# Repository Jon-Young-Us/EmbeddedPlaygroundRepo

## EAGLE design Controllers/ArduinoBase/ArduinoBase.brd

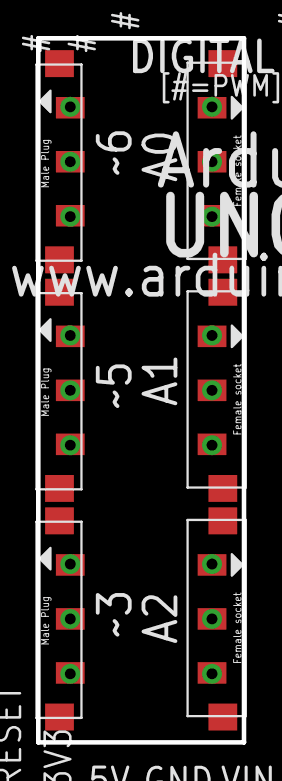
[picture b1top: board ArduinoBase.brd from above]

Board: 2 copper layers, 11.4 x 39.1 mm, 6 parts (0 on the bottom side), 2 nets, no tracks yet.

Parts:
U$1, U$5, U$6: CONN-SOCKET-3POS-3MM; SOCKET-3POS-3MM-SMD
U$2, U$3, U$4: CONN-PLUG-3POS-3MM; PLUG-3POS-3MM-SMD

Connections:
GND: U$1.GND, U$2.GND, U$3.GND, U$4.GND, U$5.GND, U$6.GND
VCC: U$1.VCC, U$2.VCC, U$3.VCC, U$4.VCC, U$5.VCC, U$6.VCC

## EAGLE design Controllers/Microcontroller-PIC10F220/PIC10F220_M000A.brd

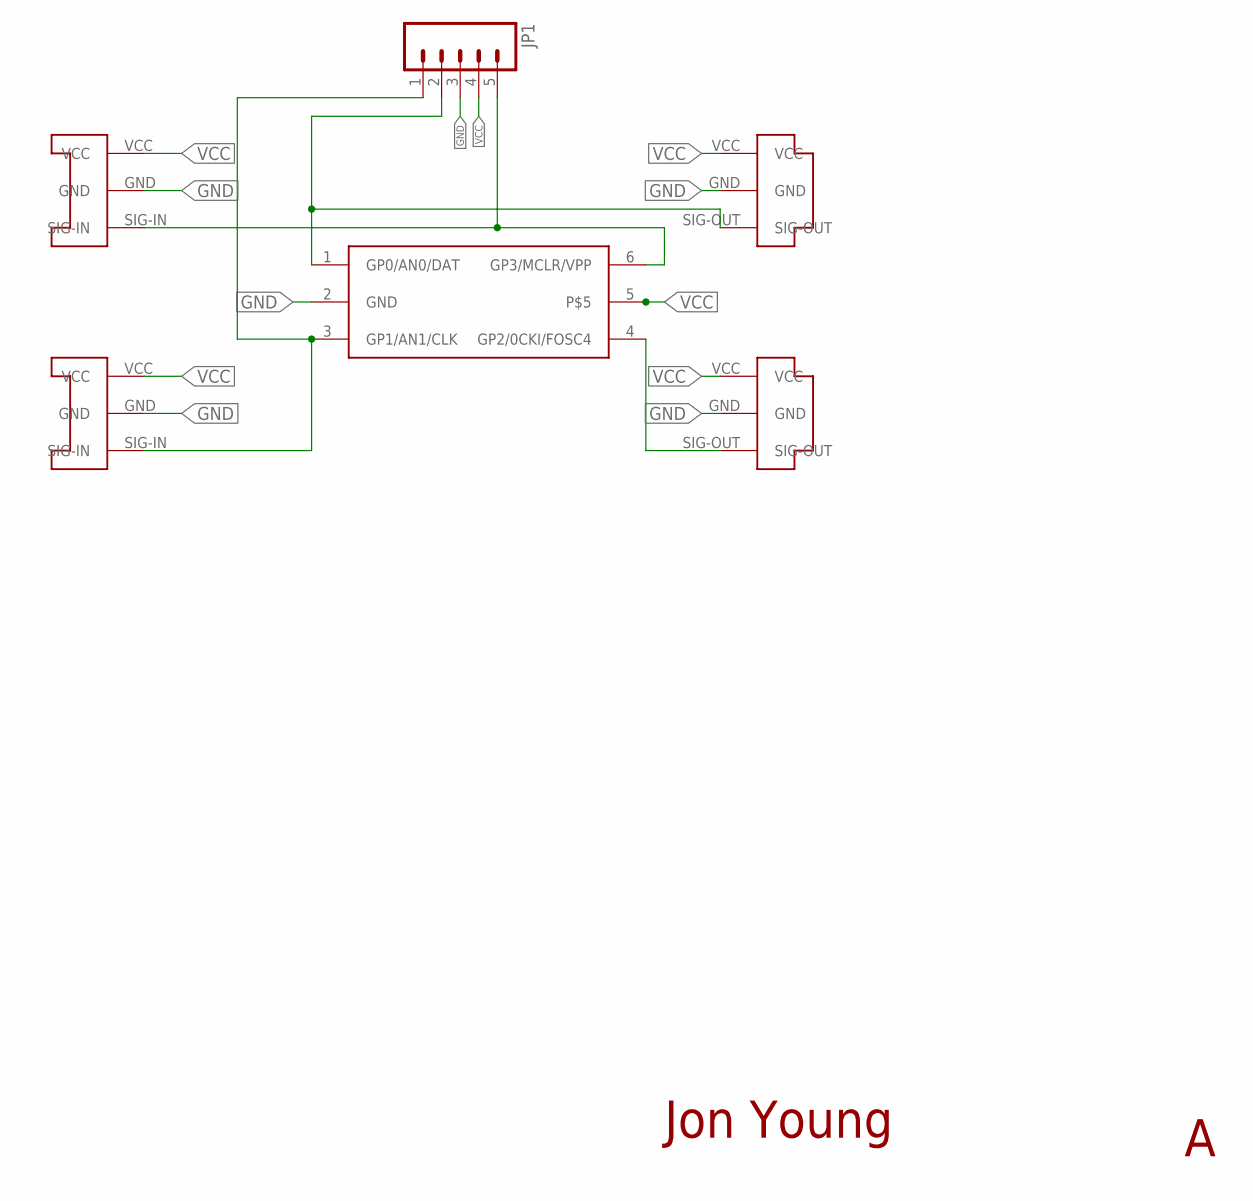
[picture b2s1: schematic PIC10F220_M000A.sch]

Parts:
JP1: M051.27MM; 1X05-1.27MM
U$1, U$4: CONN-PLUG-3POS-3MM; PLUG-3POS-3MM-SMD
U$2, U$3: CONN-SOCKET-3POS-3MM; SOCKET-3POS-3MM-SMD
U$5: PIC10F2XXT-I/OT; SOT23-6

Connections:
GND: JP1.3, U$1.GND, U$2.GND, U$3.GND, U$4.GND, U$5.2 (GND)
unnamed: U$1.SIG-OUT, U$5.4 (GP2/0CKI/FOSC4)
unnamed: JP1.1, U$2.SIG-IN, U$5.3 (GP1/AN1/CLK)
unnamed: JP1.2, U$4.SIG-OUT, U$5.1 (GP0/AN0/DAT)
unnamed: JP1.5, U$3.SIG-IN, U$5.6 (GP3/MCLR/VPP)
VCC: JP1.4, U$1.VCC, U$2.VCC, U$3.VCC, U$4.VCC, U$5.5

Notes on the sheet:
Jon Young

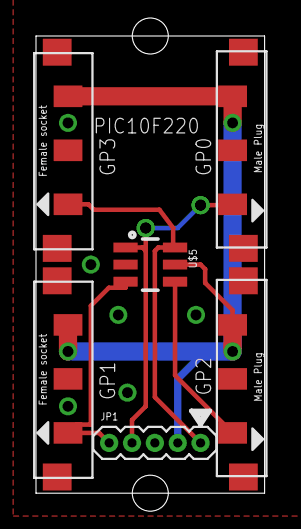
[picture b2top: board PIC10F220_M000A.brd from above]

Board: 2 copper layers, 12.7 x 25.4 mm, 6 parts (0 on the bottom side), 6 nets.

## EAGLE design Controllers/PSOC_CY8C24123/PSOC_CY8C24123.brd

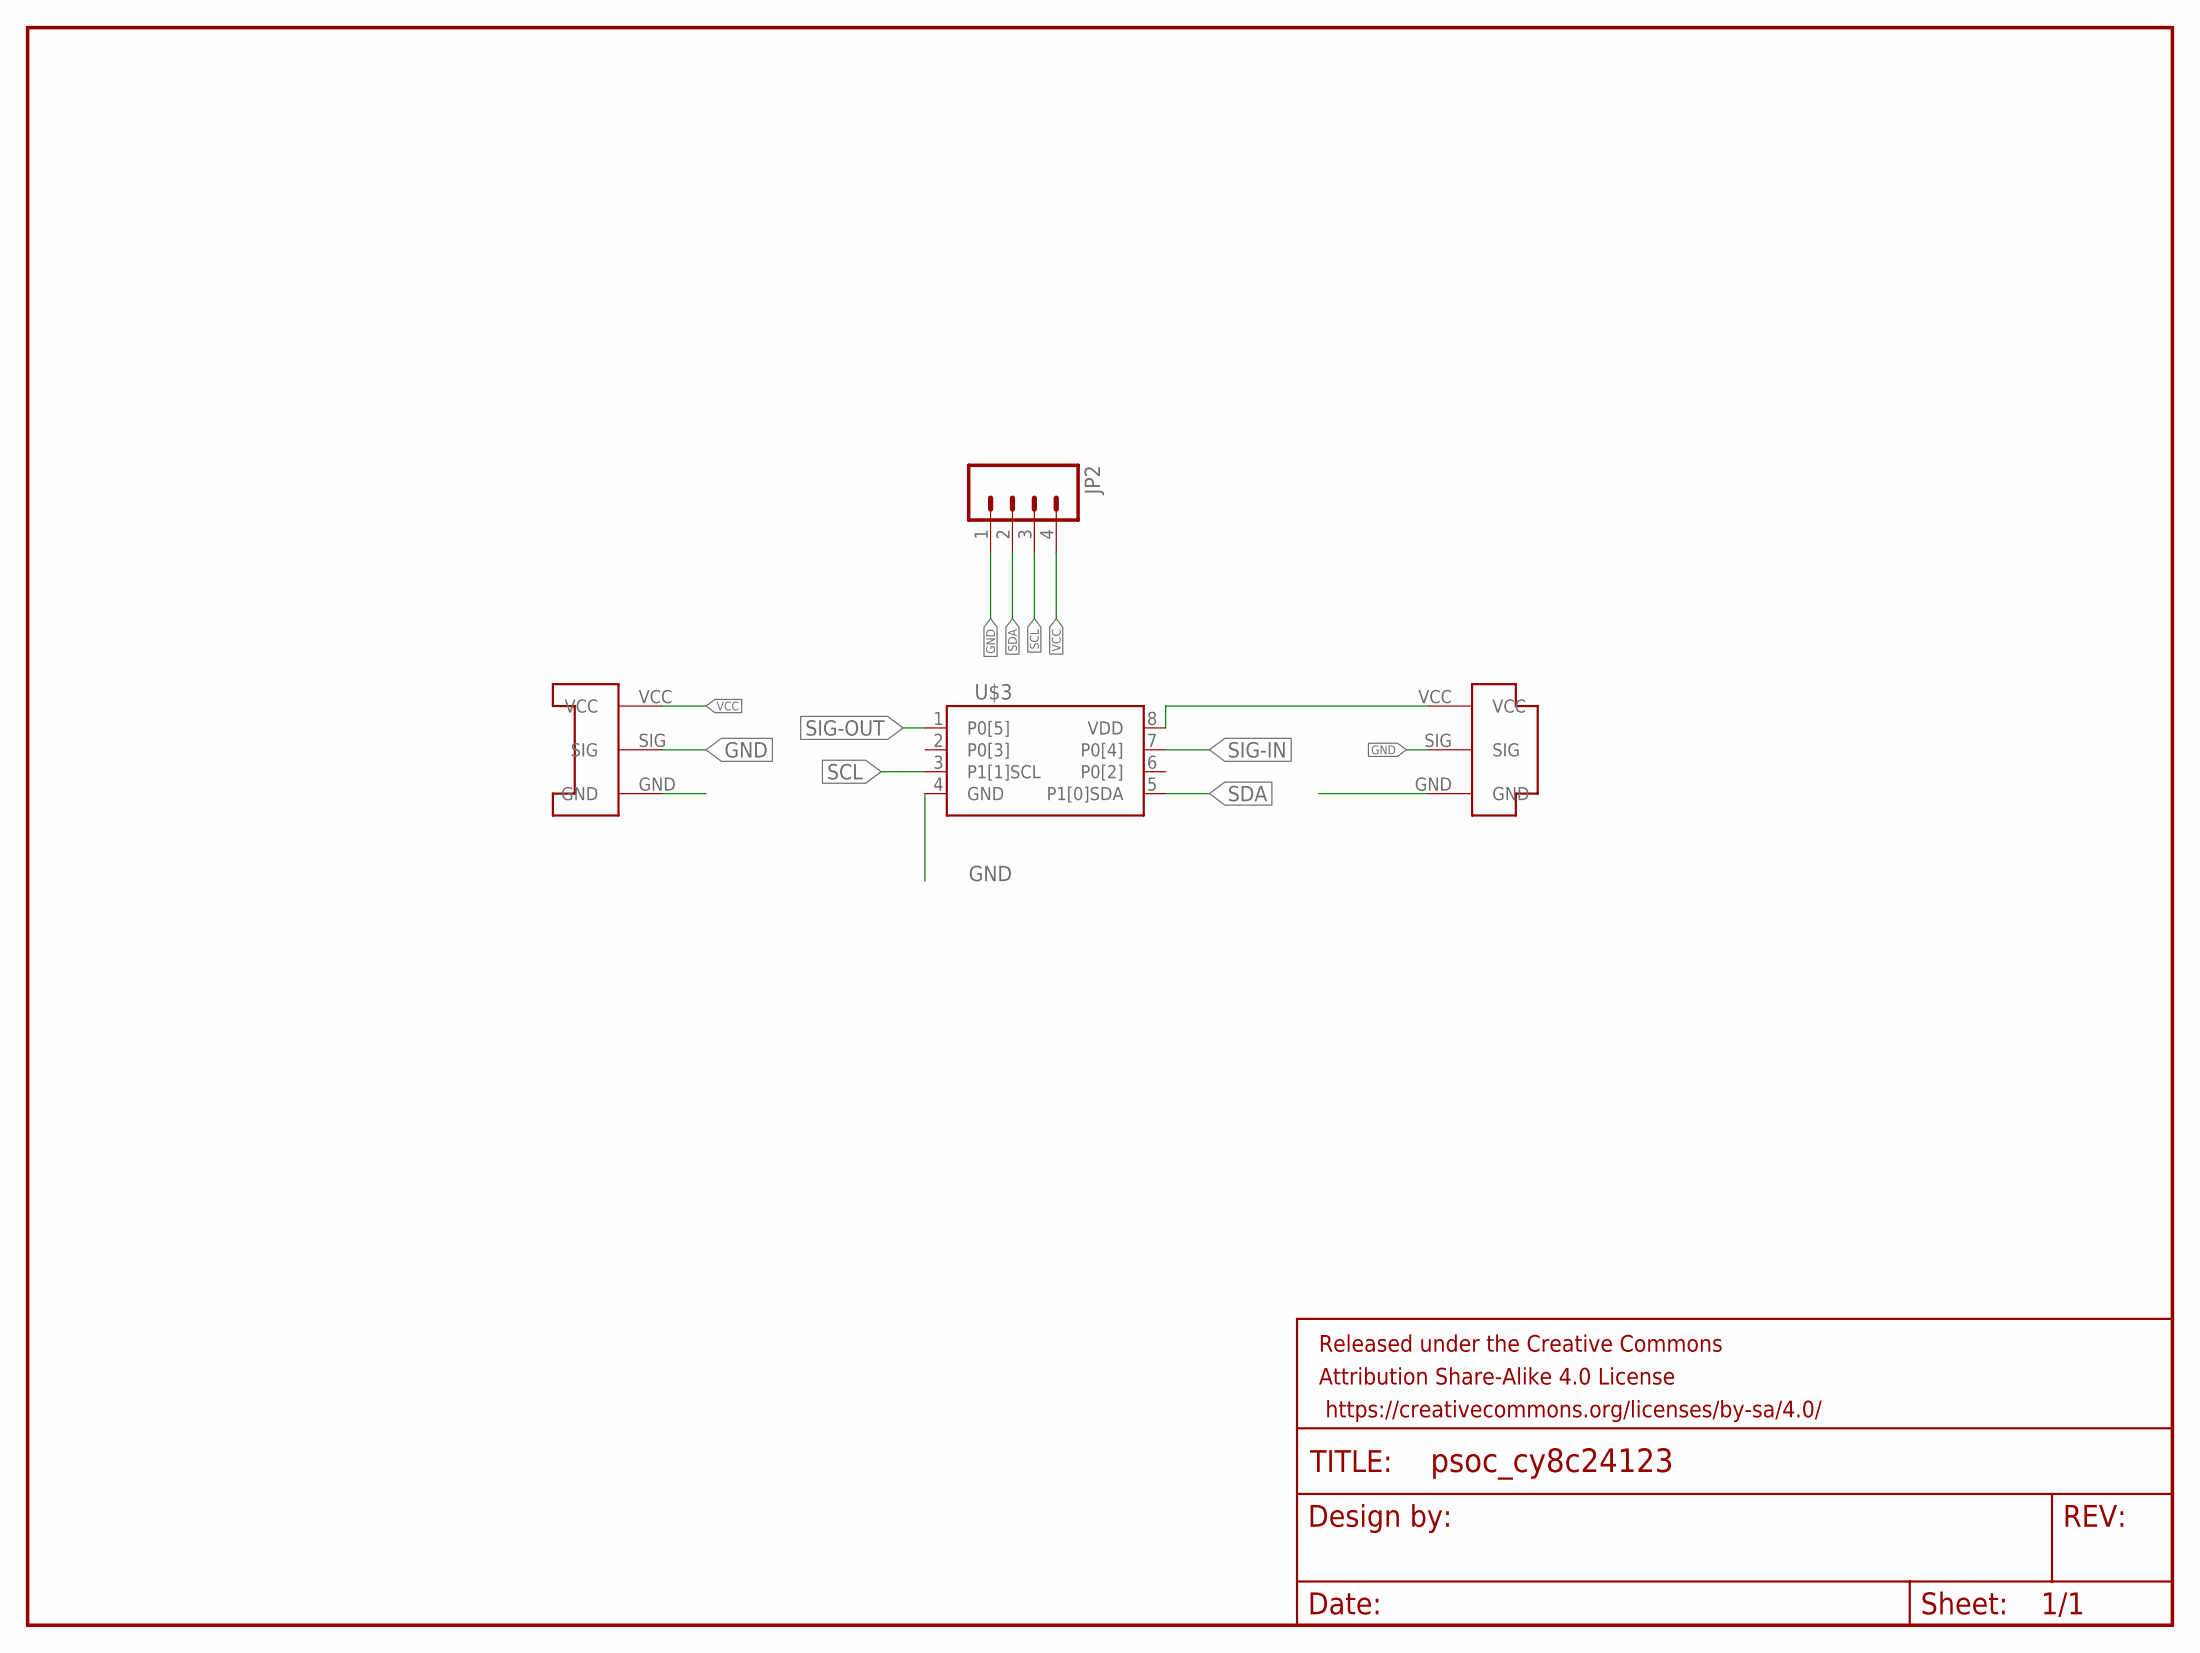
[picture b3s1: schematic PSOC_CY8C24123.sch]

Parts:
FRAME1: FRAME-LETTERNO_PACKAGE; DUMMY
JP2: M041.27MM; 1X04-1.27MM
U$1: CONN-PLUG-3POS-3MM; PLUG-3POS-3MM-SMD
U$2: CONN-SOCKET-3POS-3MM; SOCKET-3POS-3MM-SMD
U$3: CY8C24123A-24SXI; SOIC8-PSOC1

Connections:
GND: JP2.1 (VDD), U$1.SIG, U$2.SIG, U$3.4 (GND)
SCL: JP2.3 (SIG-OUT), U$3.3 (P1[1]SCL)
SDA: JP2.2 (COM-OUT), U$3.5 (P1[0]SDA)
SIG-IN: U$2.GND, U$3.7 (P0[4])
SIG-OUT: U$1.GND, U$3.1 (P0[5])
VCC: JP2.4 (GND), U$1.VCC, U$2.VCC, U$3.8 (VDD)

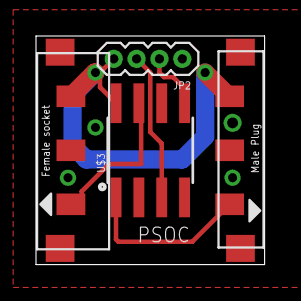
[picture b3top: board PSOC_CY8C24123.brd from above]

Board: 2 copper layers, 12.7 x 12.7 mm, 5 parts (0 on the bottom side), 6 nets.

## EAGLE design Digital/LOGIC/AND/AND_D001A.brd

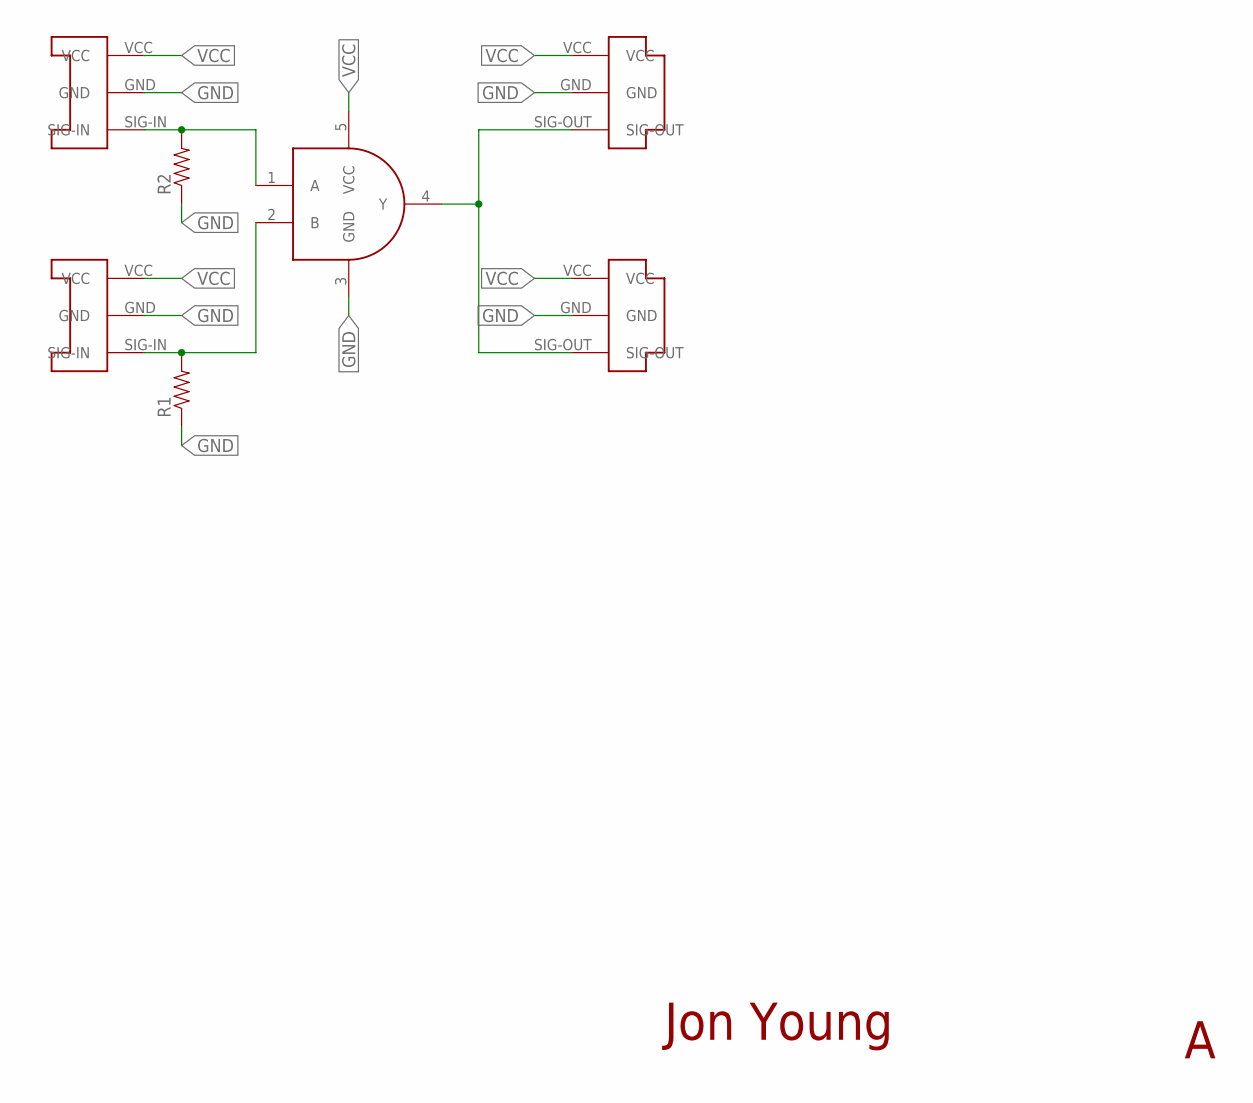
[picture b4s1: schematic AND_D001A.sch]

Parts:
R1, R2: RESISTOR0603; 0603-RES
U$1, U$4: CONN-PLUG-3POS-3MM; PLUG-3POS-3MM-SMD
U$2, U$3: CONN-SOCKET-3POS-3MM; SOCKET-3POS-3MM-SMD
U$5: AND-NC7SZ08; SC70

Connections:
GND: R1.1, R2.1, U$1.GND, U$2.GND, U$3.GND, U$4.GND, U$5.3 (GND)
unnamed: R1.2, U$2.SIG-IN, U$5.2 (B)
unnamed: R2.2, U$3.SIG-IN, U$5.1 (A)
SIG-OUT: U$1.SIG-OUT, U$4.SIG-OUT, U$5.4 (Y)
VCC: U$1.VCC, U$2.VCC, U$3.VCC, U$4.VCC, U$5.5 (VCC)

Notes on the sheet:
Jon Young

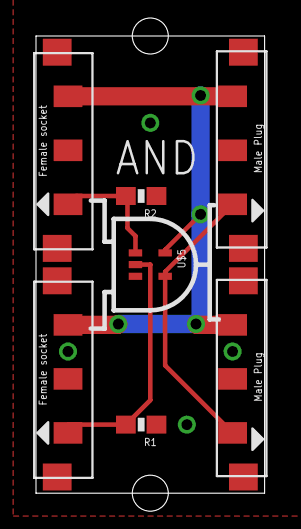
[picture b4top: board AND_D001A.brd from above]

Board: 2 copper layers, 12.7 x 25.4 mm, 7 parts (0 on the bottom side), 5 nets.

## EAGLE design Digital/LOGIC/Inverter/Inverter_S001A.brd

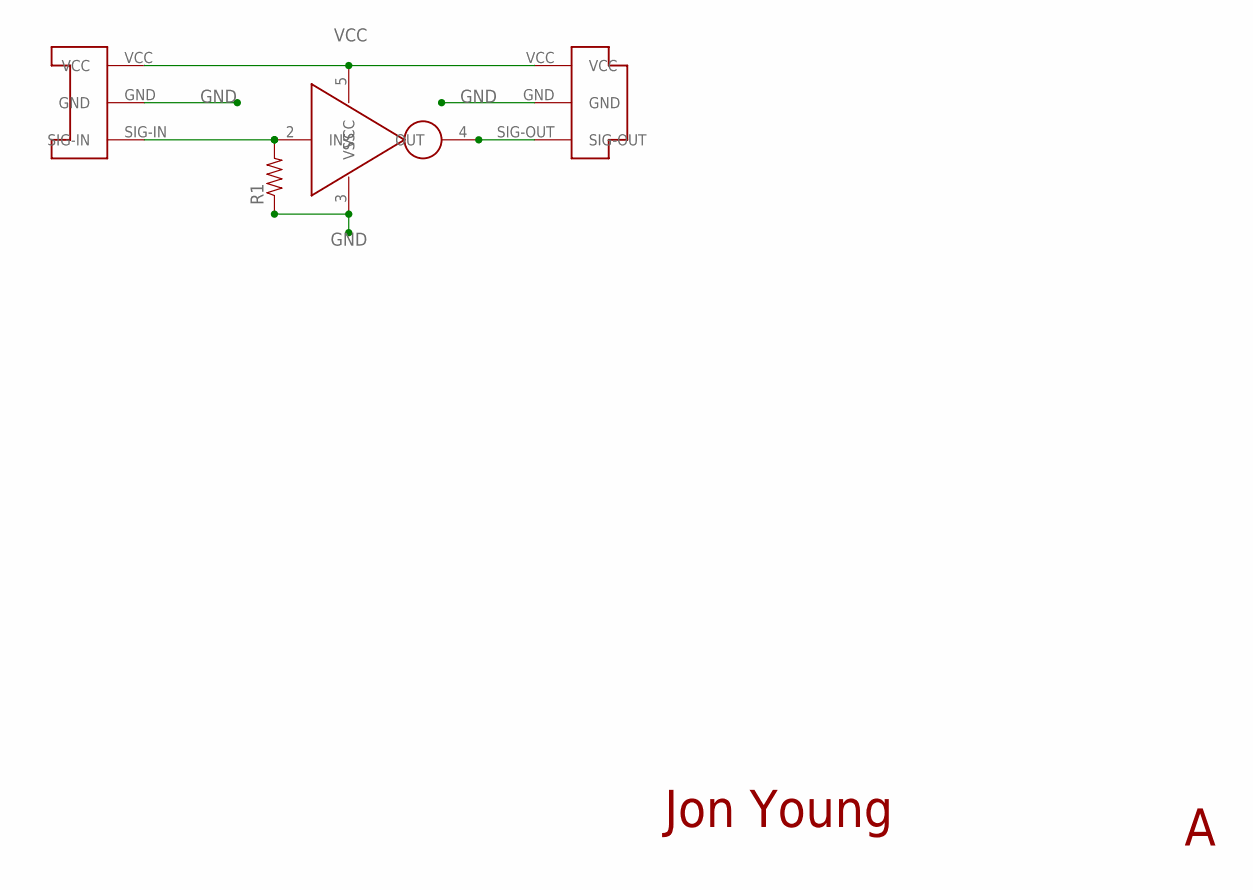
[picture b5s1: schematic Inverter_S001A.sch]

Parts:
R1: RESISTOR0603; 0603-RES
U$1: CONN-PLUG-3POS-3MM; PLUG-3POS-3MM-SMD
U$2: CONN-SOCKET-3POS-3MM; SOCKET-3POS-3MM-SMD
U$3: INV-NC7S145XCT-ND; SC70

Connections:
GND: R1.1, U$1.GND, U$2.GND, U$3.3 (VSS)
unnamed: U$1.SIG-OUT, U$3.4 (OUT)
unnamed: R1.2, U$2.SIG-IN, U$3.2 (IN)
VCC: U$1.VCC, U$2.VCC, U$3.5 (VCC)

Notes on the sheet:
Jon Young

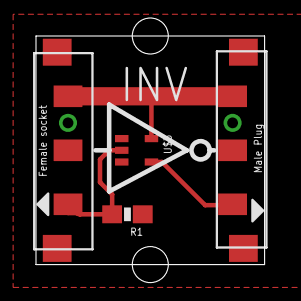
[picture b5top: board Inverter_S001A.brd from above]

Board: 2 copper layers, 12.7 x 12.7 mm, 4 parts (0 on the bottom side), 4 nets.

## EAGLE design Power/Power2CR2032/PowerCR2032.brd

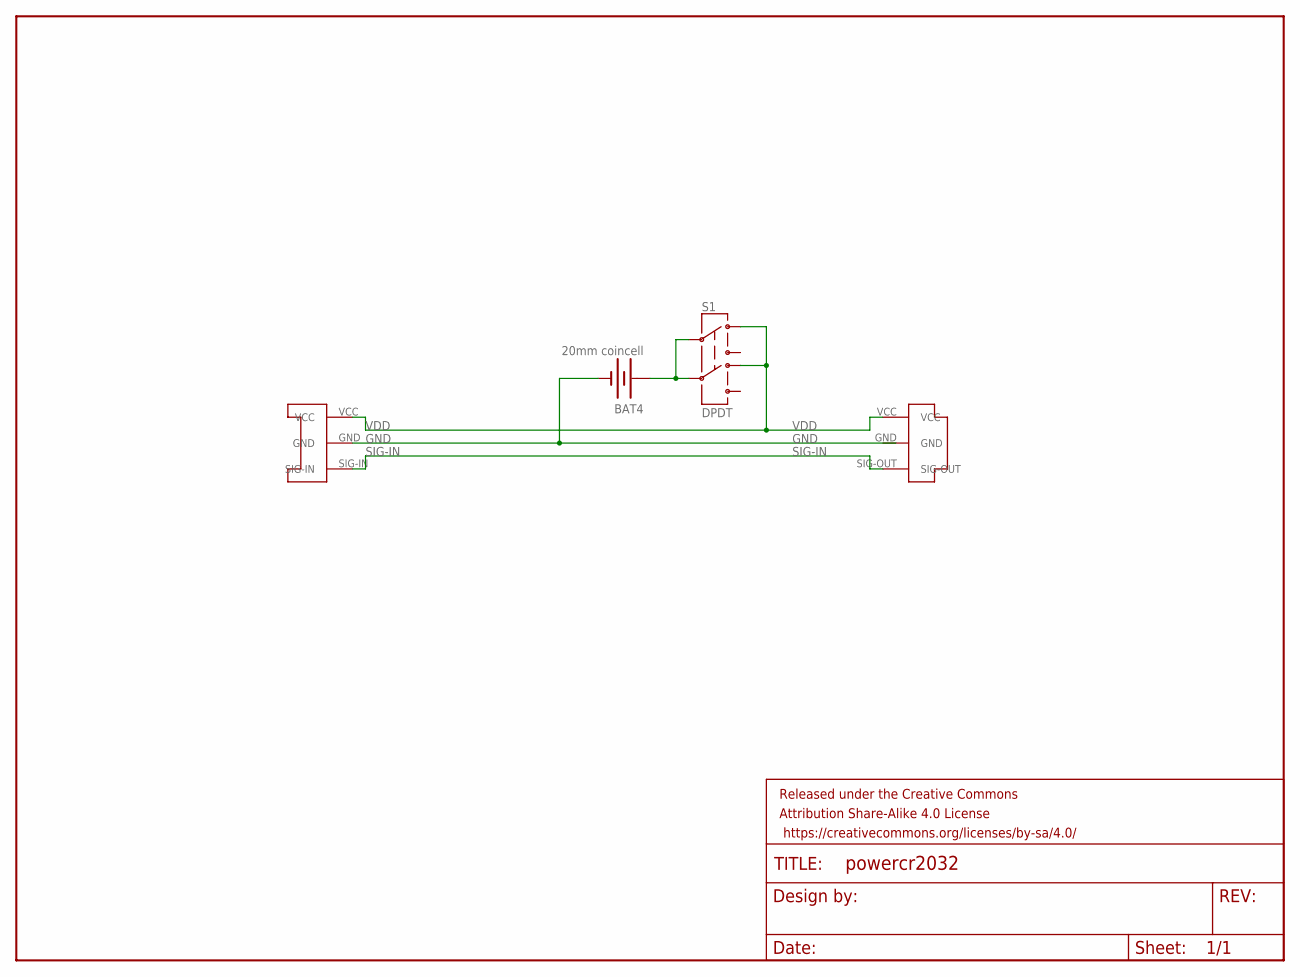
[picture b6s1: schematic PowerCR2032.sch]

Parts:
BAT4: 20mm coincell; BATTCON_20MM_4LEGS
FRAME1: FRAME-LETTERNO_PACKAGE; DUMMY
S1: DPDT; AYZ0202
U$1: CONN-SOCKET-3POS-3MM; SOCKET-3POS-3MM-SMD
U$2: CONN-PLUG-3POS-3MM; PLUG-3POS-3MM-SMD

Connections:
GND: BAT4.2 (-), U$1.GND, U$2.GND
SIG-IN: U$1.SIG-IN, U$2.SIG-OUT
VBAT: BAT4.1 (+), S1.2, S1.5
VDD: S1.1, S1.4, U$1.VCC, U$2.VCC

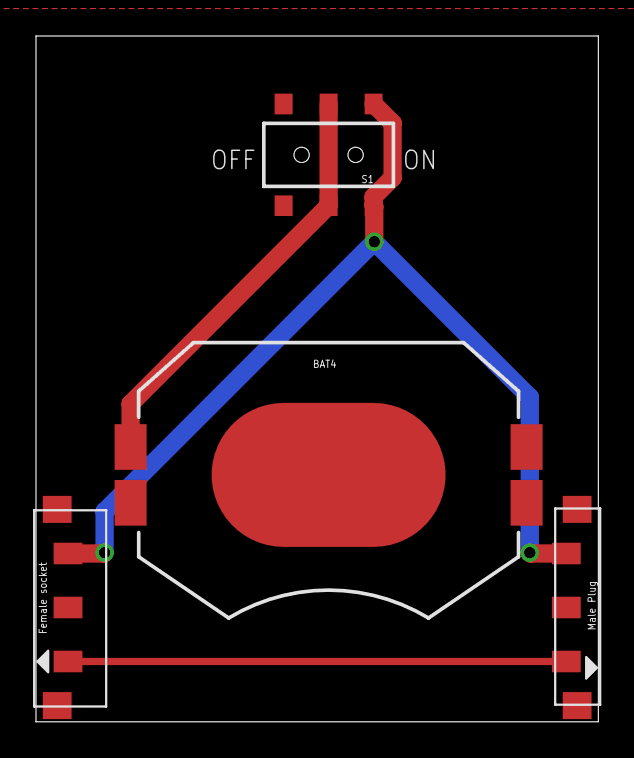
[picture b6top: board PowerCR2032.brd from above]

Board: 2 copper layers, 31.2 x 38.1 mm, 5 parts (0 on the bottom side), 4 nets.

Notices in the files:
parts and their libraries:
SparkFun-Connectors: Licensing: Creative Commons ShareAlike 4.0 International - https://creativecommons.org/licenses/by-sa/4.0
SparkFun-Aesthetics: Released under the Creative Commons Attribution Share-Alike 4.0 License
SparkFun-Aesthetics: https://creativecommons.org/licenses/by-sa/4.0
